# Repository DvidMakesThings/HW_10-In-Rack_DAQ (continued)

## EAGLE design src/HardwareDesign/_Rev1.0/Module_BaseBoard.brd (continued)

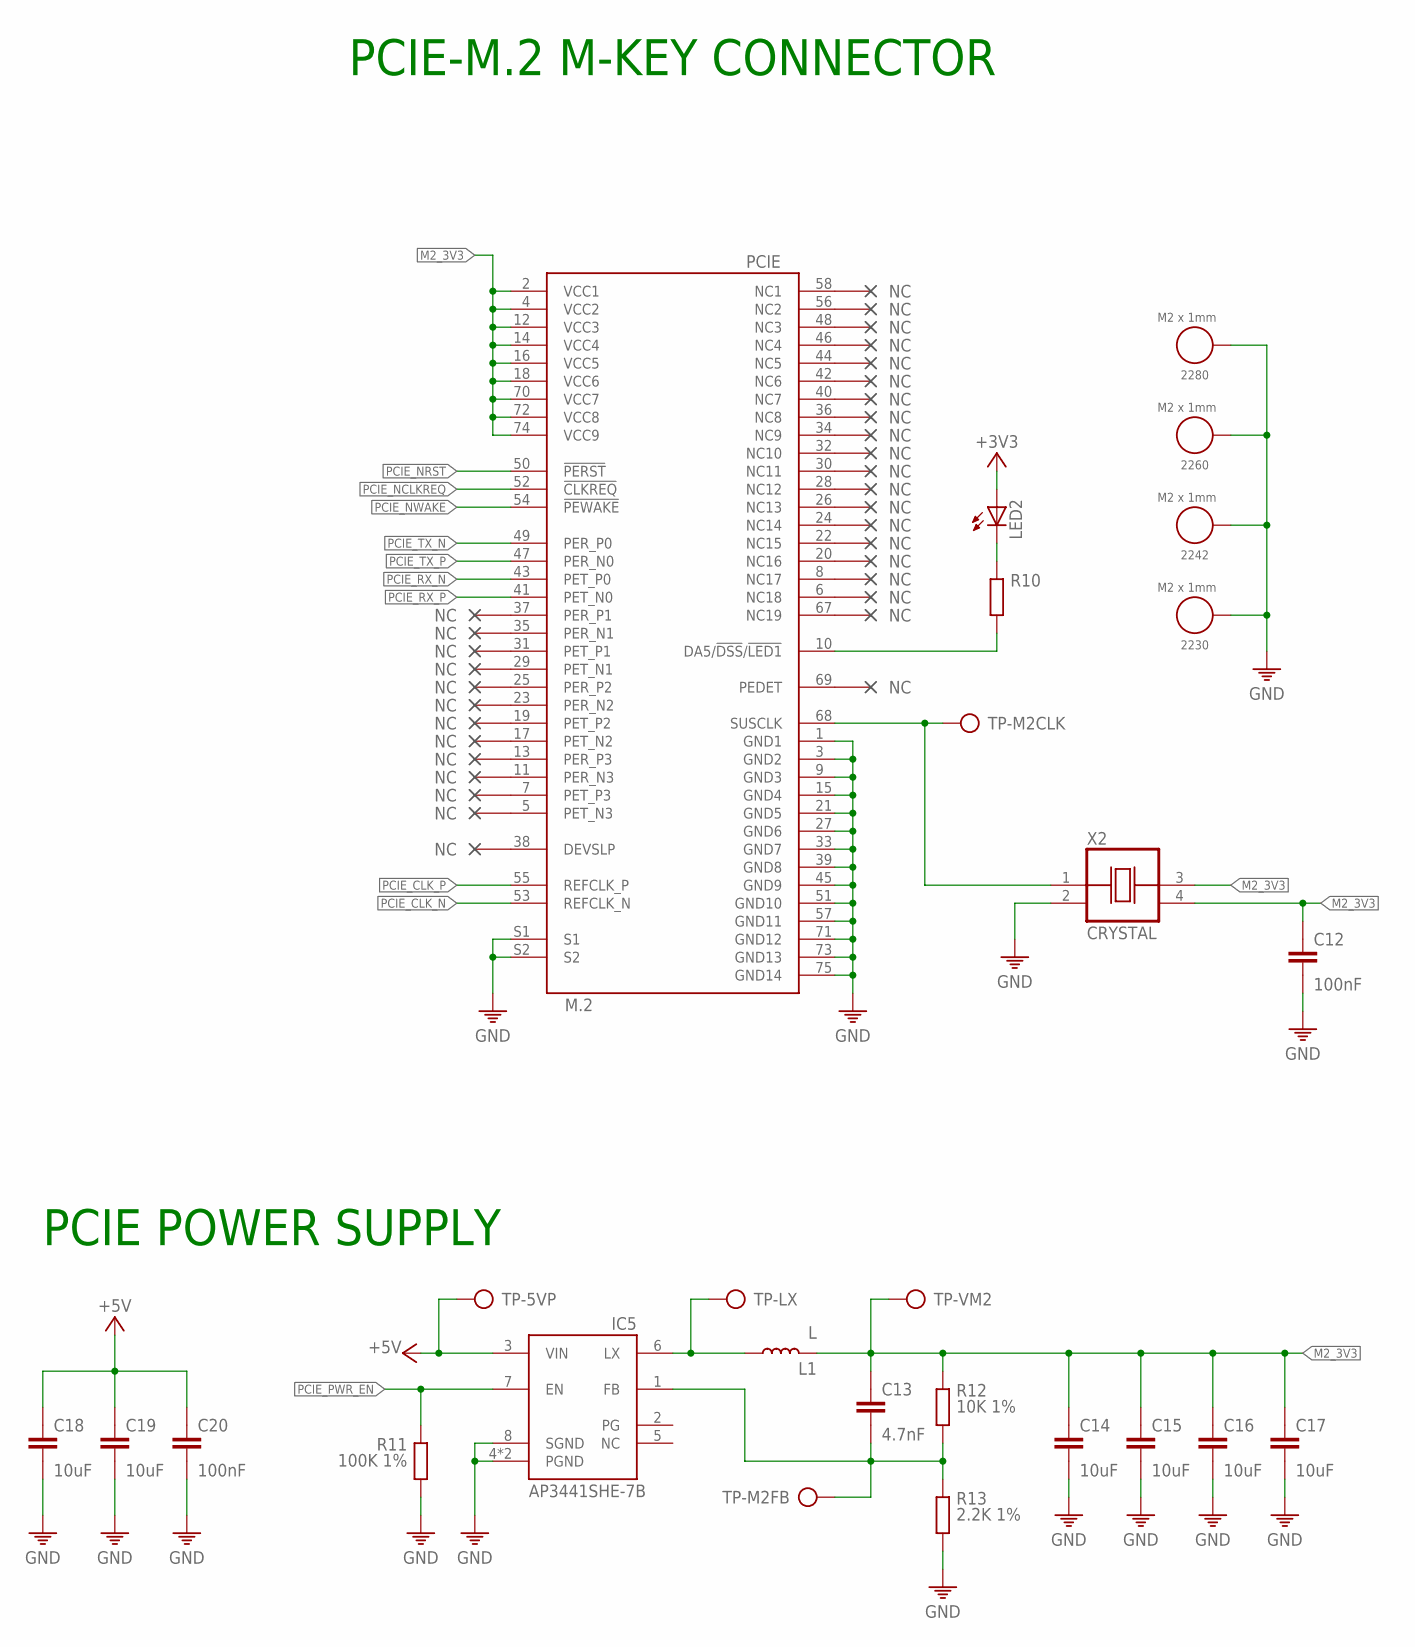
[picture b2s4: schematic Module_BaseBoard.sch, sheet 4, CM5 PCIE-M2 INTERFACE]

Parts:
2230, 2242, 2260, 2280: M2 x 1mm; WA-SMSI_9774010243
C12, C20: 100nF; C0402
C13: 4.7nF; C0402
C14, C15, C16, C17, C18, C19: 10uF; C0805
IC5: AP3441SHE-7B; SON50P201X201X56-9T90X170N
L1: L; SRR5228A
LED2: LEDCHIPLED_0805; CHIPLED_0805
PCIE: M.2
R10: R0402; 0402
R11: 100K 1%; 0402
R12: 10K 1%; 0402
R13: 2.2K 1%; 0402
TP-5VP: TP
TP-LX: TP
TP-M2CLK, TP-M2FB: TP
TP-VM2: TP
X2: CRYSTAL; OSCCC500X320X130

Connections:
+3V3: LED2.A; also elsewhere on the board
+5V: C18.1, C19.1, C20.1, IC5.3 (VIN), TP-5VP.TP; also elsewhere on the board
GND: 2230.1, 2242.1, 2260.1, 2280.1, C12.2, C14.2, C15.2, C16.2, C17.2, C18.2, C19.2, C20.2, IC5.4 (PGND), IC5.8 (SGND), IC5.9 (PGND), PCIE.1 (GND1), PCIE.3 (GND2), PCIE.9 (GND3), PCIE.15 (GND4), PCIE.21 (GND5), PCIE.27 (GND6), PCIE.33 (GND7), PCIE.39 (GND8), PCIE.45 (GND9), PCIE.51 (GND10), PCIE.57 (GND11), PCIE.71 (GND12), PCIE.73 (GND13), PCIE.75 (GND14), PCIE.S1, PCIE.S2, R11.2, R13.2, X2.2 (VSS); also elsewhere on the board
M2_3V3: C12.1, C13.1, C14.1, C15.1, C16.1, C17.1, L1.2, PCIE.2 (VCC1), PCIE.4 (VCC2), PCIE.12 (VCC3), PCIE.14 (VCC4), PCIE.16 (VCC5), PCIE.18 (VCC6), PCIE.70 (VCC7), PCIE.72 (VCC8), PCIE.74 (VCC9), R12.1, TP-VM2.TP, X2.3 (OUT), X2.4 (VDD)
unnamed: PCIE.10 (DA5/!DSS!/!LED1), R10.2
unnamed: LED2.C, R10.1
unnamed: IC5.6 (LX), L1.1, TP-LX.TP
unnamed: C13.2, IC5.1 (FB), R12.2, R13.1, TP-M2FB.TP
unnamed: PCIE.68 (SUSCLK), TP-M2CLK.TP, X2.1 (CON)
PCIE_CLK_N: PCIE.53 (REFCLK_N); also elsewhere on the board
PCIE_CLK_P: PCIE.55 (REFCLK_P); also elsewhere on the board
PCIE_NCLKREQ: PCIE.52 (!CLKREQ); also elsewhere on the board
PCIE_NRST: PCIE.50 (!PERST); also elsewhere on the board
PCIE_NWAKE: PCIE.54 (!PEWAKE); also elsewhere on the board
PCIE_PWR_EN: IC5.7 (EN), R11.1; also elsewhere on the board
PCIE_RX_N: PCIE.43 (PET_P0); also elsewhere on the board
PCIE_RX_P: PCIE.41 (PET_N0); also elsewhere on the board
PCIE_TX_N: PCIE.49 (PER_P0); also elsewhere on the board
PCIE_TX_P: PCIE.47 (PER_N0); also elsewhere on the board

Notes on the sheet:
PCIE-M.2 M-KEY CONNECTOR
PCIE POWER SUPPLY

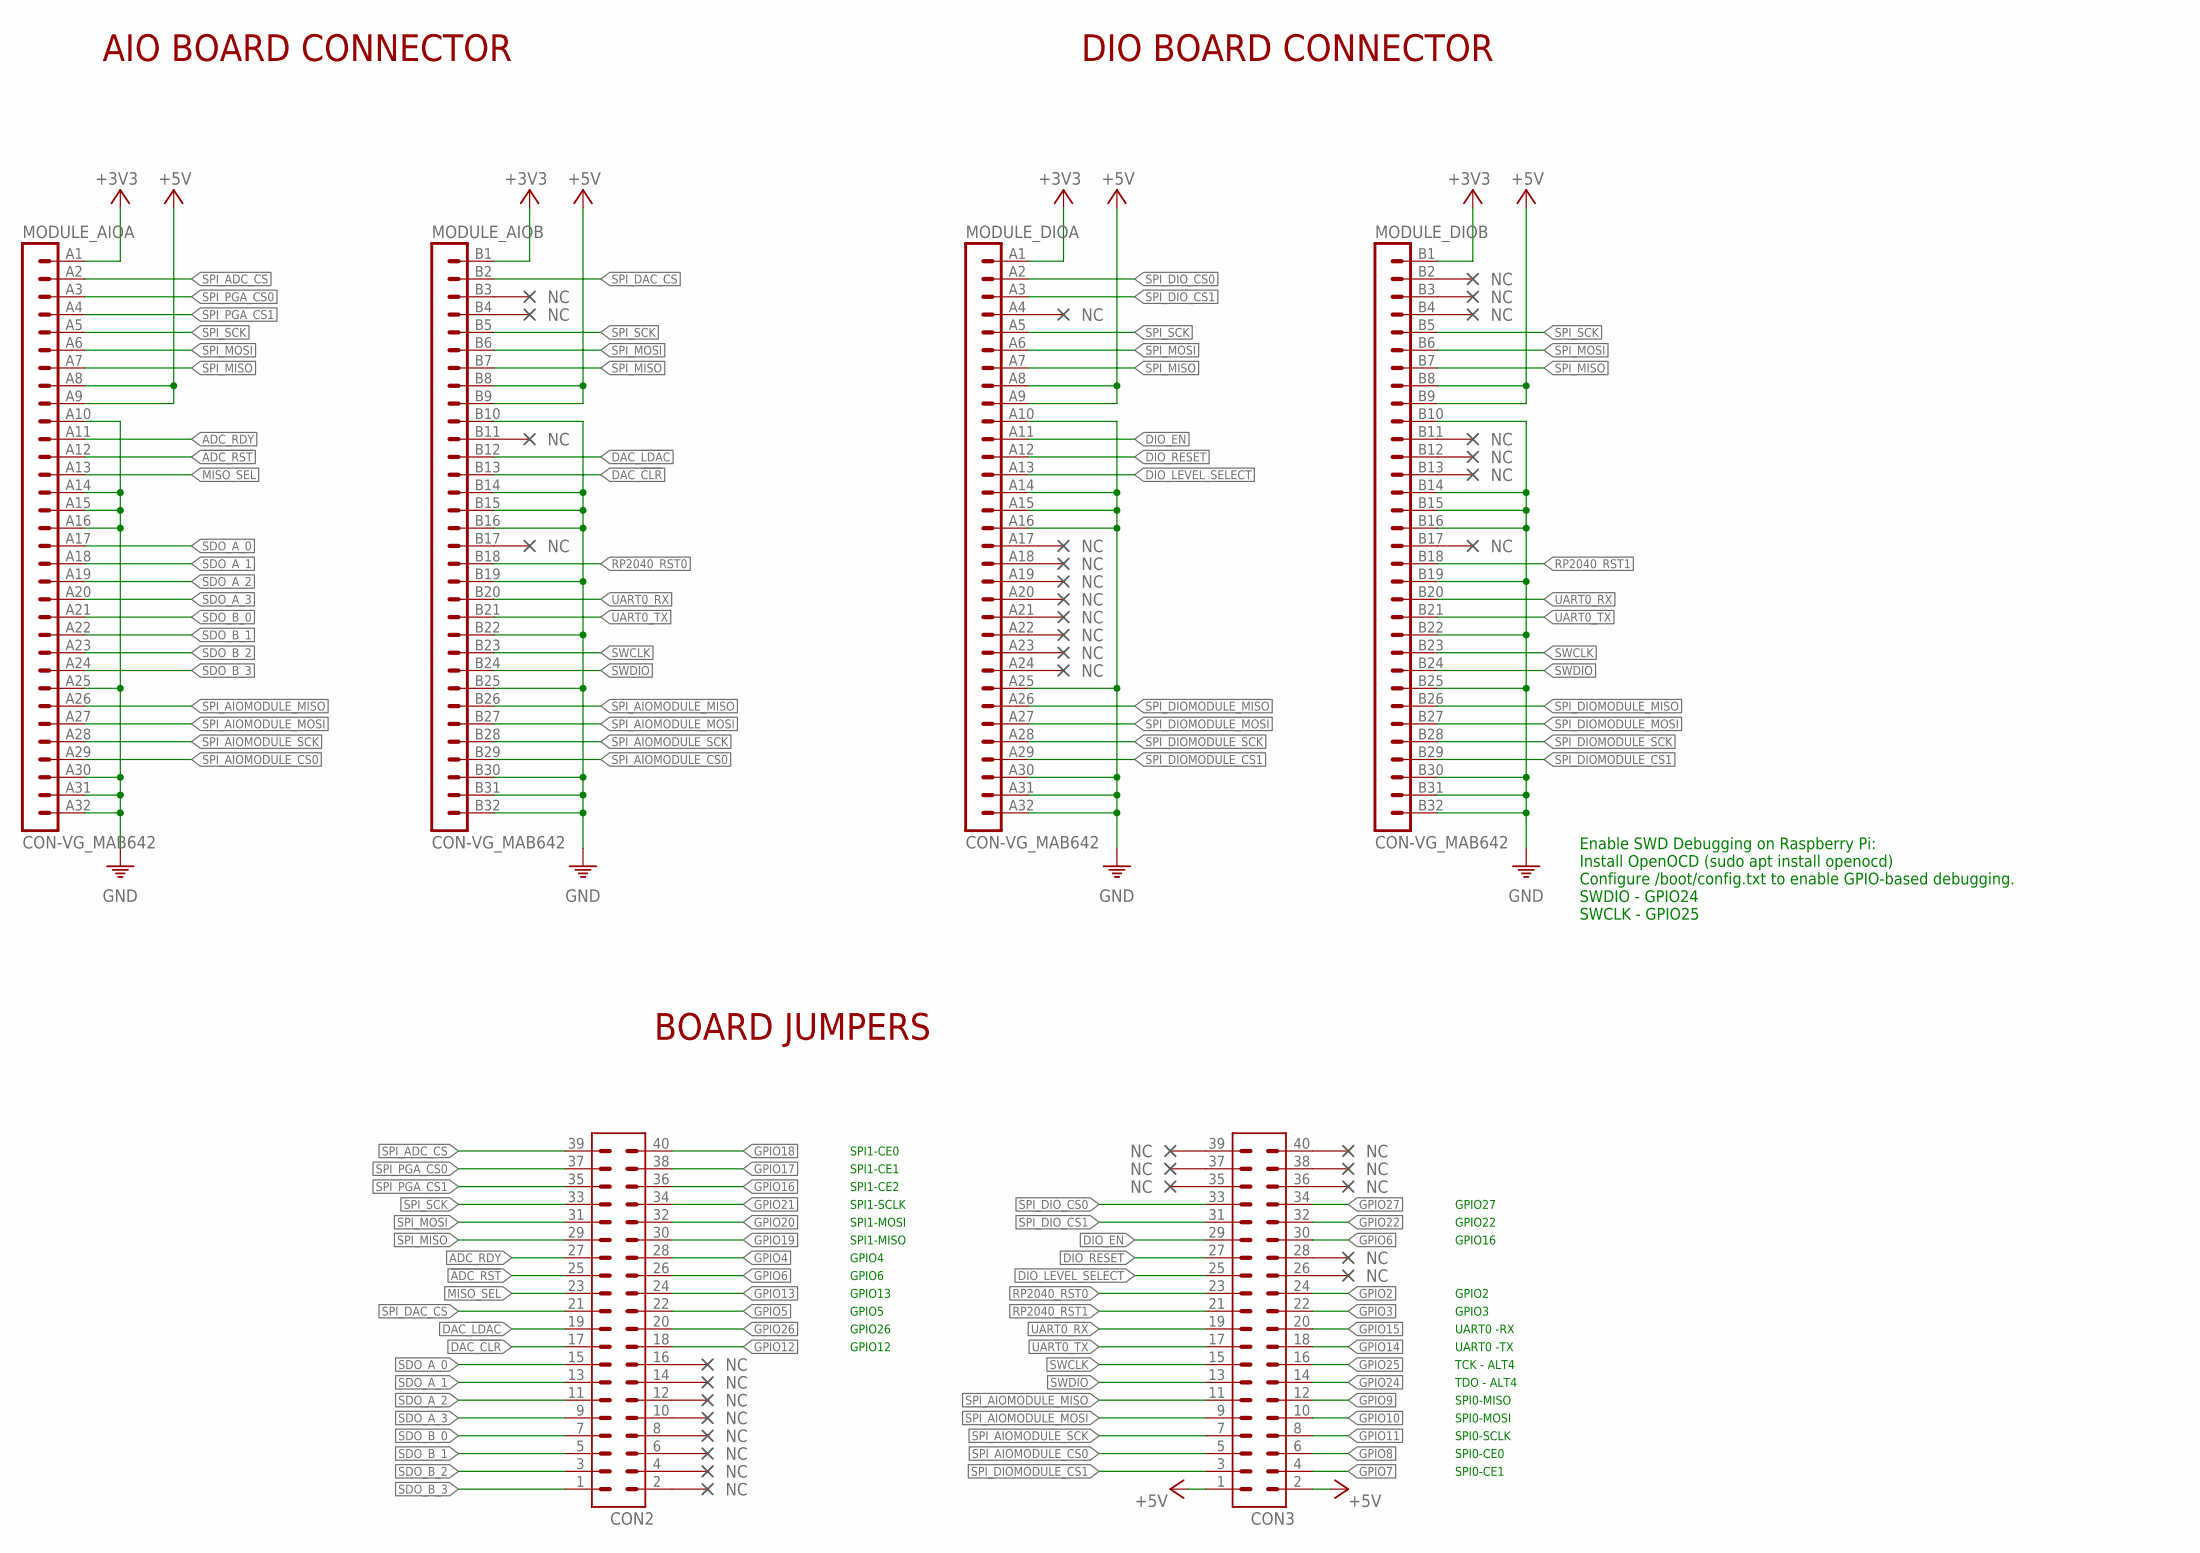
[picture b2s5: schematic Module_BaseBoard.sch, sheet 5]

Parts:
CON2, CON3: CON-2X20; 2X20
MODULE_AIO: CON-VG_MAB642; CON-VG-MAB64-RECEPTACLE
MODULE_DIO: CON-VG_MAB642; CON-VG-MAB64-RECEPTACLE

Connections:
!ADC_RST: CON2.25, MODULE_AIO.A12 (12)
+3V3: MODULE_AIO.A1 (1), MODULE_AIO.B1 (1), MODULE_DIO.A1 (1), MODULE_DIO.B1 (1); also elsewhere on the board
+5V: CON3.1, CON3.2, MODULE_AIO.A8 (8), MODULE_AIO.A9 (9), MODULE_AIO.B8 (8), MODULE_AIO.B9 (9), MODULE_DIO.A8 (8), MODULE_DIO.A9 (9), MODULE_DIO.B8 (8), MODULE_DIO.B9 (9); also elsewhere on the board
ADC_RDY: CON2.27, MODULE_AIO.A11 (11)
DAC_!CLR: CON2.17, MODULE_AIO.B13 (13)
DAC_!LDAC: CON2.19, MODULE_AIO.B12 (12)
DIO_EN: CON3.29, MODULE_DIO.A11 (11)
DIO_LEVEL_SELECT: CON3.25, MODULE_DIO.A13 (13)
DIO_RESET: CON3.27, MODULE_DIO.A12 (12)
GND: MODULE_AIO.A10 (10), MODULE_AIO.A14 (14), MODULE_AIO.A15 (15), MODULE_AIO.A16 (16), MODULE_AIO.A25 (25), MODULE_AIO.A30 (30), MODULE_AIO.A31 (31), MODULE_AIO.A32 (32), MODULE_AIO.B10 (10), MODULE_AIO.B14 (14), MODULE_AIO.B15 (15), MODULE_AIO.B16 (16), MODULE_AIO.B19 (19), MODULE_AIO.B22 (22), MODULE_AIO.B25 (25), MODULE_AIO.B30 (30), MODULE_AIO.B31 (31), MODULE_AIO.B32 (32), MODULE_DIO.A10 (10), MODULE_DIO.A14 (14), MODULE_DIO.A15 (15), MODULE_DIO.A16 (16), MODULE_DIO.A25 (25), MODULE_DIO.A30 (30), MODULE_DIO.A31 (31), MODULE_DIO.A32 (32), MODULE_DIO.B10 (10), MODULE_DIO.B14 (14), MODULE_DIO.B15 (15), MODULE_DIO.B16 (16), MODULE_DIO.B19 (19), MODULE_DIO.B22 (22), MODULE_DIO.B25 (25), MODULE_DIO.B30 (30), MODULE_DIO.B31 (31), MODULE_DIO.B32 (32); also elsewhere on the board
GPIO2: CON3.24; also elsewhere on the board
GPIO3: CON3.22; also elsewhere on the board
GPIO4: CON2.28; also elsewhere on the board
GPIO5: CON2.22; also elsewhere on the board
GPIO6: CON2.26, CON3.30; also elsewhere on the board
GPIO7: CON3.4; also elsewhere on the board
GPIO8: CON3.6; also elsewhere on the board
GPIO9: CON3.12; also elsewhere on the board
GPIO10: CON3.10; also elsewhere on the board
GPIO11: CON3.8; also elsewhere on the board
GPIO12: CON2.18; also elsewhere on the board
GPIO13: CON2.24; also elsewhere on the board
GPIO14: CON3.18; also elsewhere on the board
GPIO15: CON3.20; also elsewhere on the board
GPIO16: CON2.36; also elsewhere on the board
GPIO17: CON2.38; also elsewhere on the board
GPIO18: CON2.40; also elsewhere on the board
GPIO19: CON2.30; also elsewhere on the board
GPIO20: CON2.32; also elsewhere on the board
GPIO21: CON2.34; also elsewhere on the board
GPIO22: CON3.32; also elsewhere on the board
GPIO24: CON3.14; also elsewhere on the board
GPIO25: CON3.16; also elsewhere on the board
GPIO26: CON2.20; also elsewhere on the board
GPIO27: CON3.34; also elsewhere on the board
MISO_SEL: CON2.23, MODULE_AIO.A13 (13)
RP2040_RST0: CON3.23, MODULE_AIO.B18 (18)
RP2040_RST1: CON3.21, MODULE_DIO.B18 (18)
SDO_A_0: CON2.15, MODULE_AIO.A17 (17)
SDO_A_1: CON2.13, MODULE_AIO.A18 (18)
SDO_A_2: CON2.11, MODULE_AIO.A19 (19)
SDO_A_3: CON2.9, MODULE_AIO.A20 (20)
SDO_B_0: CON2.7, MODULE_AIO.A21 (21)
SDO_B_1: CON2.5, MODULE_AIO.A22 (22)
SDO_B_2: CON2.3, MODULE_AIO.A23 (23)
SDO_B_3: CON2.1, MODULE_AIO.A24 (24)
SPI_ADC_CS: CON2.39, MODULE_AIO.A2 (2)
SPI_AIOMODULE_CS0: CON3.5, MODULE_AIO.A29 (29), MODULE_AIO.B29 (29)
SPI_AIOMODULE_MISO: CON3.11, MODULE_AIO.A26 (26), MODULE_AIO.B26 (26)
SPI_AIOMODULE_MOSI: CON3.9, MODULE_AIO.A27 (27), MODULE_AIO.B27 (27)
SPI_AIOMODULE_SCK: CON3.7, MODULE_AIO.A28 (28), MODULE_AIO.B28 (28)
SPI_DAC_CS: CON2.21, MODULE_AIO.B2 (2)
SPI_DIOMODULE_CS1: CON3.3, MODULE_DIO.A29 (29), MODULE_DIO.B29 (29)
SPI_DIOMODULE_MISO: MODULE_DIO.A26 (26), MODULE_DIO.B26 (26)
SPI_DIOMODULE_MOSI: MODULE_DIO.A27 (27), MODULE_DIO.B27 (27)
SPI_DIOMODULE_SCK: MODULE_DIO.A28 (28), MODULE_DIO.B28 (28)
SPI_DIO_CS0: CON3.33, MODULE_DIO.A2 (2)
SPI_DIO_CS1: CON3.31, MODULE_DIO.A3 (3)
SPI_MISO: CON2.29, MODULE_AIO.A7 (7), MODULE_AIO.B7 (7), MODULE_DIO.A7 (7), MODULE_DIO.B7 (7)
SPI_MOSI: CON2.31, MODULE_AIO.A6 (6), MODULE_AIO.B6 (6), MODULE_DIO.A6 (6), MODULE_DIO.B6 (6)
SPI_PGA_CS0: CON2.37, MODULE_AIO.A3 (3)
SPI_PGA_CS1: CON2.35, MODULE_AIO.A4 (4)
SPI_SCK: CON2.33, MODULE_AIO.A5 (5), MODULE_AIO.B5 (5), MODULE_DIO.A5 (5), MODULE_DIO.B5 (5)
SWCLK: CON3.15, MODULE_AIO.B23 (23), MODULE_DIO.B23 (23)
SWDIO: CON3.13, MODULE_AIO.B24 (24), MODULE_DIO.B24 (24)
UART0_RX: CON3.19, MODULE_AIO.B20 (20), MODULE_DIO.B20 (20)
UART0_TX: CON3.17, MODULE_AIO.B21 (21), MODULE_DIO.B21 (21)

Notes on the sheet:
AIO BOARD CONNECTOR
Enable SWD Debugging on Raspberry Pi: Install OpenOCD (sudo apt install openocd) Configure /boot/config.txt to enable GPIO-based debugging. SWDIO - GPIO24 SWCLK - GPIO25
DIO BOARD CONNECTOR
BOARD JUMPERS
SPI1-CE0
SPI1-CE1
SPI1-CE2
SPI1-SCLK
SPI1-MOSI
SPI1-MISO
GPIO5
GPIO27
GPIO22
TDO - ALT4
TCK - ALT4
UART0 -RX
UART0 -TX
SPI0-MISO
SPI0-MOSI
SPI0-SCLK
SPI0-CE0
SPI0-CE1
GPIO4
GPIO6
GPIO13
GPIO26
GPIO12
GPIO16
GPIO2
GPIO3

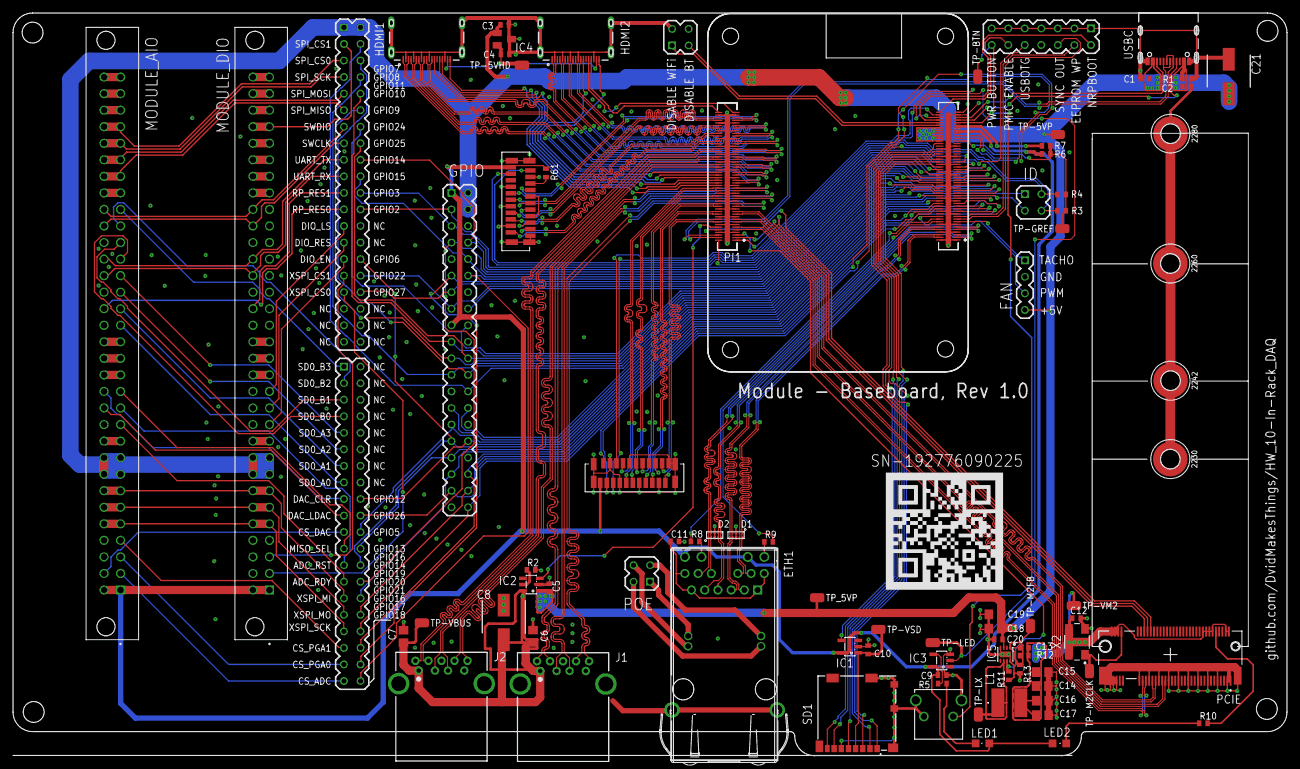
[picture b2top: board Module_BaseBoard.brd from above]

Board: 4 copper layers, 195.6 x 114.0 mm, 84 parts (0 on the bottom side), 197 nets.

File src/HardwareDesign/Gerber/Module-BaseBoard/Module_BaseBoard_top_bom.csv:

Comment,Designator,Footprint,LCSC Part #
,C1 C2,C0402,
,LED2,CHIPLED_0805,
,PI1,CM5,
,R10,0402,
,SD1,MICROSD,
0R,R6,0402,
1K,R5,0402,
2.2K 1%,R1 R3 R4 R13 R61,0402,
4.7nF,C13,C0402,
10K 1%,R12,0402,
10uF,C6 C7 C14 C15 C16 C17 C18 C19,C0805,
15K 1%,R2,0402,
74LVC1G07,IC3,SOT23-5,
100K 1%,R11,0402,
100nF,C3 C4 C5 C9 C10 C11 C12 C20,C0402,
100uF 16V,C8 C21,100UF-16V,
470R,R8 R9,0402,
629722000214,USBC,629722000214,
685119136923,HDMI1 HDMI2,685119136923,
AP3441SHE-7B,IC5,SON50P201X201X56-9T90X170N,
AP22653W6,IC2,SOT23-6,
CRYSTAL,X2,OSCCC500X320X130,
DNI,R7,0402,
FH12-22S-0.5SVA,J3 J4,FH12-22S-0.5SH,
Green,LED1,CHIPLED_0805,
L,L1,SRR5228A,
M.2,PCIE,M.2,
M2 x 1mm,2230 2242 2260 2280,WA-SMSI_9774010243,
RT9742GGJ,IC1,SOT23-5,
RT9742NGV,IC4,SOT23,
TP,TP-5VHD TP-5VP TP-BTN TP-GREF TP-LED TP-LX TP-M2CLK TP-M2FB TP-VBUS TP-VM2 TP-VSD TP_5VP,TP,
TPD4EUSB30,D1 D2,USON,

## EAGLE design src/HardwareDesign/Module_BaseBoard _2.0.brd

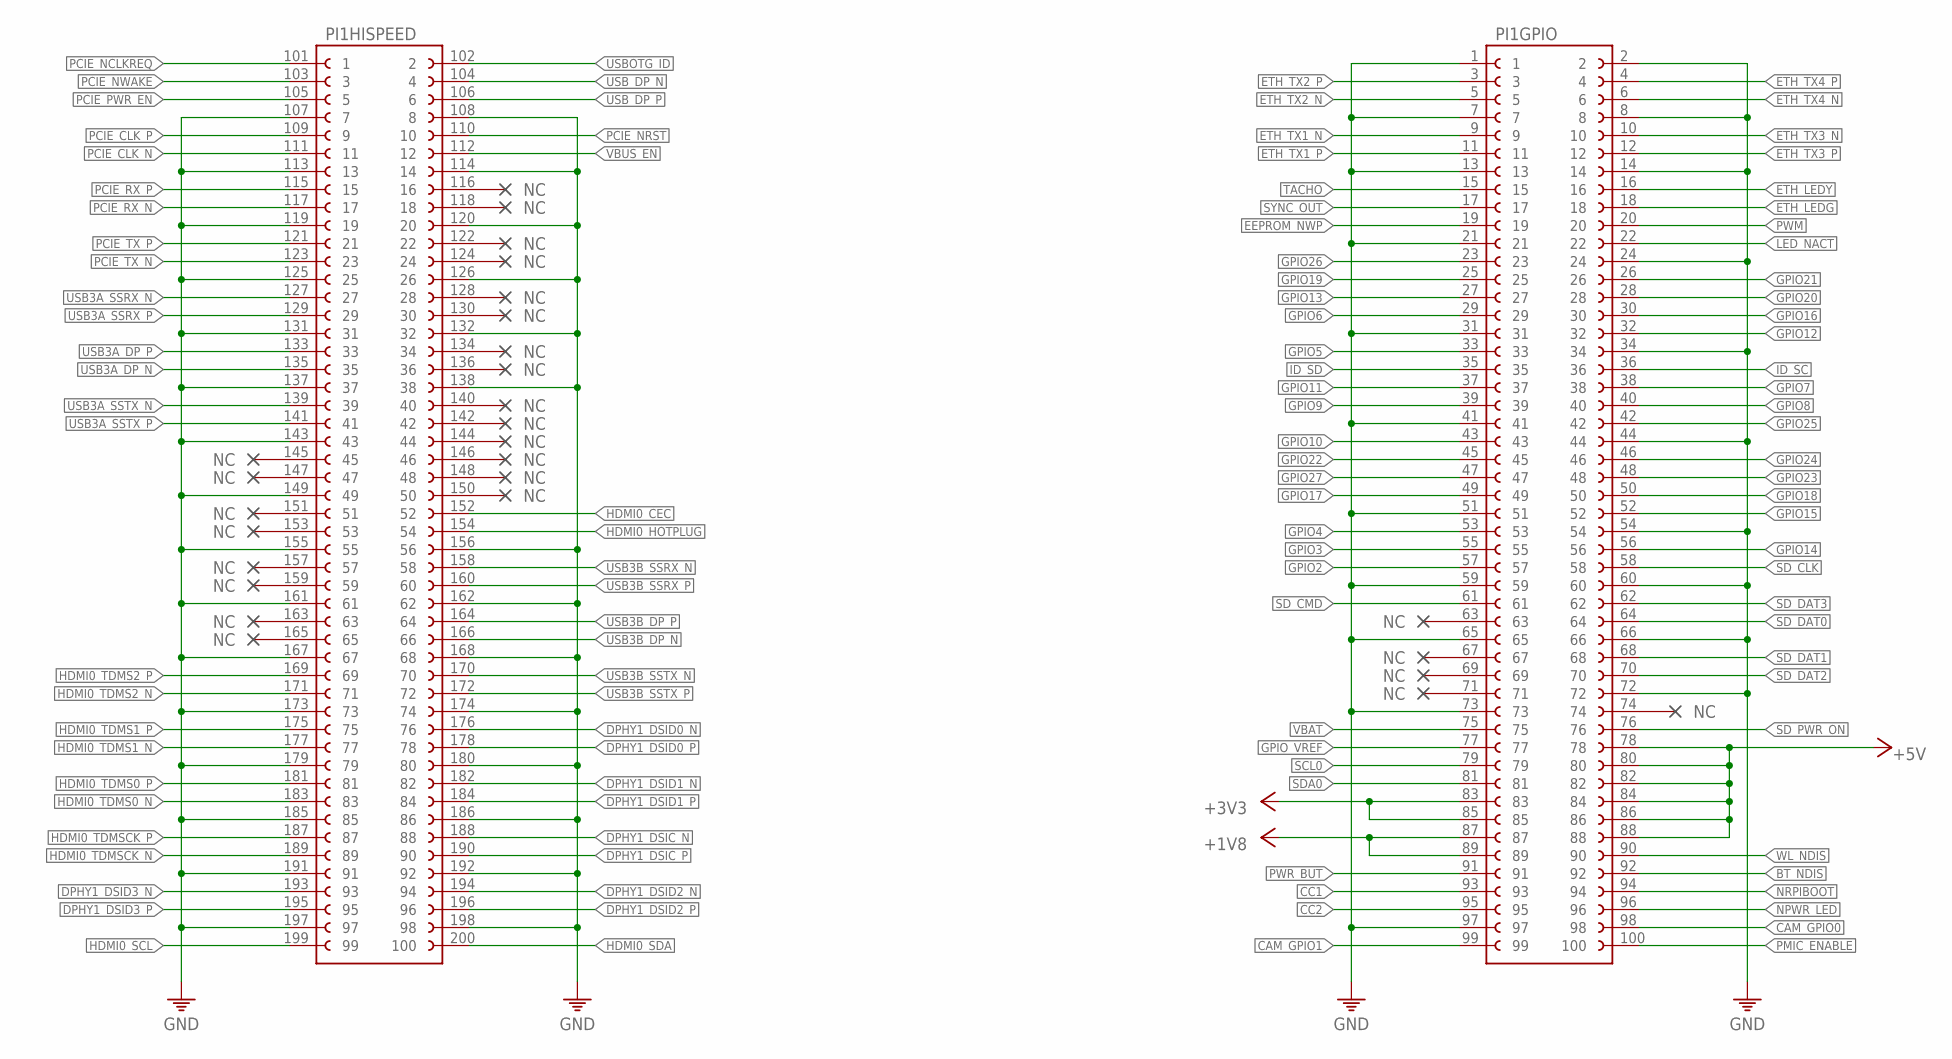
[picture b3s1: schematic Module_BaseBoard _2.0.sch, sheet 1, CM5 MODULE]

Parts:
PI1: RASPBERRY_CM5; CM5

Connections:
+1V8: PI1.87, PI1.89; also elsewhere on the board
+3V3: PI1.83, PI1.85; also elsewhere on the board
+5V: PI1.78, PI1.80, PI1.82, PI1.84, PI1.86, PI1.88; also elsewhere on the board
BT_NDIS: PI1.92
CAM_GPIO0: PI1.98; also elsewhere on the board
CAM_GPIO1: PI1.99; also elsewhere on the board
CC1: PI1.93; also elsewhere on the board
CC2: PI1.95; also elsewhere on the board
DPHY1_DSIC_N: PI1.188 (88); also elsewhere on the board
DPHY1_DSIC_P: PI1.190 (90); also elsewhere on the board
DPHY1_DSID0_N: PI1.176 (76); also elsewhere on the board
DPHY1_DSID0_P: PI1.178 (78); also elsewhere on the board
DPHY1_DSID1_N: PI1.182 (82); also elsewhere on the board
DPHY1_DSID1_P: PI1.184 (84); also elsewhere on the board
DPHY1_DSID2_N: PI1.194 (94); also elsewhere on the board
DPHY1_DSID2_P: PI1.196 (96); also elsewhere on the board
DPHY1_DSID3_N: PI1.193 (93); also elsewhere on the board
DPHY1_DSID3_P: PI1.195 (95); also elsewhere on the board
EEPROM_NWP: PI1.19; also elsewhere on the board
ETH_LEDG: PI1.18; also elsewhere on the board
ETH_LEDY: PI1.16; also elsewhere on the board
ETH_TX1_N: PI1.9; also elsewhere on the board
ETH_TX1_P: PI1.11; also elsewhere on the board
ETH_TX2_N: PI1.5; also elsewhere on the board
ETH_TX2_P: PI1.3; also elsewhere on the board
ETH_TX3_N: PI1.10; also elsewhere on the board
ETH_TX3_P: PI1.12; also elsewhere on the board
ETH_TX4_N: PI1.6; also elsewhere on the board
ETH_TX4_P: PI1.4; also elsewhere on the board
GND: PI1.1, PI1.2, PI1.7, PI1.8, PI1.13, PI1.14, PI1.21, PI1.24, PI1.31, PI1.34, PI1.41, PI1.44, PI1.51, PI1.54, PI1.59, PI1.60, PI1.65, PI1.66, PI1.72, PI1.73, PI1.97, PI1.107 (7), PI1.108 (8), PI1.113 (13), PI1.114 (14), PI1.119 (19), PI1.120 (20), PI1.125 (25), PI1.126 (26), PI1.131 (31), PI1.132 (32), PI1.137 (37), PI1.138 (38), PI1.143 (43), PI1.149 (49), PI1.155 (55), PI1.156 (56), PI1.161 (61), PI1.162 (62), PI1.167 (67), PI1.168 (68), PI1.173 (73), PI1.174 (74), PI1.179 (79), PI1.180 (80), PI1.185 (85), PI1.186 (86), PI1.191 (91), PI1.192 (92), PI1.197 (97), PI1.198 (98); also elsewhere on the board
GPIO2: PI1.57; also elsewhere on the board
GPIO3: PI1.55; also elsewhere on the board
GPIO4: PI1.53; also elsewhere on the board
GPIO5: PI1.33; also elsewhere on the board
GPIO6: PI1.29; also elsewhere on the board
GPIO7: PI1.38; also elsewhere on the board
GPIO8: PI1.40; also elsewhere on the board
GPIO9: PI1.39; also elsewhere on the board
GPIO10: PI1.43; also elsewhere on the board
GPIO11: PI1.37; also elsewhere on the board
GPIO12: PI1.32; also elsewhere on the board
GPIO13: PI1.27; also elsewhere on the board
GPIO14: PI1.56; also elsewhere on the board
GPIO15: PI1.52; also elsewhere on the board
GPIO16: PI1.30; also elsewhere on the board
GPIO17: PI1.49; also elsewhere on the board
GPIO18: PI1.50; also elsewhere on the board
GPIO19: PI1.25; also elsewhere on the board
GPIO20: PI1.28; also elsewhere on the board
GPIO21: PI1.26; also elsewhere on the board
GPIO22: PI1.45; also elsewhere on the board
GPIO23: PI1.48; also elsewhere on the board
GPIO24: PI1.46; also elsewhere on the board
GPIO25: PI1.42; also elsewhere on the board
GPIO26: PI1.23; also elsewhere on the board
GPIO27: PI1.47; also elsewhere on the board
GPIO_VREF: PI1.77; also elsewhere on the board
HDMI0_CEC: PI1.152 (52); also elsewhere on the board
HDMI0_HOTPLUG: PI1.154 (54); also elsewhere on the board
HDMI0_SCL: PI1.199 (99); also elsewhere on the board
HDMI0_SDA: PI1.200 (100); also elsewhere on the board
HDMI0_TDMS0_N: PI1.183 (83); also elsewhere on the board
HDMI0_TDMS0_P: PI1.181 (81); also elsewhere on the board
HDMI0_TDMS1_N: PI1.177 (77); also elsewhere on the board
HDMI0_TDMS1_P: PI1.175 (75); also elsewhere on the board
HDMI0_TDMS2_N: PI1.171 (71); also elsewhere on the board
HDMI0_TDMS2_P: PI1.169 (69); also elsewhere on the board
HDMI0_TDMSCK_N: PI1.189 (89); also elsewhere on the board
HDMI0_TDMSCK_P: PI1.187 (87); also elsewhere on the board
ID_SC: PI1.36; also elsewhere on the board
ID_SD: PI1.35; also elsewhere on the board
LED_NACT: PI1.22; also elsewhere on the board
NPWR_LED: PI1.96; also elsewhere on the board
NRPIBOOT: PI1.94; also elsewhere on the board
PCIE_CLK_N: PI1.111 (11); also elsewhere on the board
PCIE_CLK_P: PI1.109 (9); also elsewhere on the board
PCIE_NCLKREQ: PI1.101 (1); also elsewhere on the board
PCIE_NRST: PI1.110 (10); also elsewhere on the board
PCIE_NWAKE: PI1.103 (3); also elsewhere on the board
PCIE_PWR_EN: PI1.105 (5); also elsewhere on the board
PCIE_RX_N: PI1.117 (17); also elsewhere on the board
PCIE_RX_P: PI1.115 (15); also elsewhere on the board
PCIE_TX_N: PI1.123 (23); also elsewhere on the board
PCIE_TX_P: PI1.121 (21); also elsewhere on the board
PMIC_ENABLE: PI1.100; also elsewhere on the board
PWM: PI1.20
PWR_BUT: PI1.91; also elsewhere on the board
SCL0: PI1.79
SDA0: PI1.81
SD_CLK: PI1.58; also elsewhere on the board
SD_CMD: PI1.61; also elsewhere on the board
SD_DAT0: PI1.64; also elsewhere on the board
SD_DAT1: PI1.68; also elsewhere on the board
SD_DAT2: PI1.70; also elsewhere on the board
SD_DAT3: PI1.62; also elsewhere on the board
SD_PWR_ON: PI1.76; also elsewhere on the board
SYNC_OUT: PI1.17; also elsewhere on the board
TACHO: PI1.15
USB3A_DP_N: PI1.135 (35); also elsewhere on the board
USB3A_DP_P: PI1.133 (33); also elsewhere on the board
USB3A_SSRX_N: PI1.127 (27); also elsewhere on the board
USB3A_SSRX_P: PI1.129 (29); also elsewhere on the board
USB3A_SSTX_N: PI1.139 (39); also elsewhere on the board
USB3A_SSTX_P: PI1.141 (41); also elsewhere on the board
USB3B_DP_N: PI1.166 (66); also elsewhere on the board
USB3B_DP_P: PI1.164 (64); also elsewhere on the board
USB3B_SSRX_N: PI1.158 (58); also elsewhere on the board
USB3B_SSRX_P: PI1.160 (60); also elsewhere on the board
USB3B_SSTX_N: PI1.170 (70); also elsewhere on the board
USB3B_SSTX_P: PI1.172 (72); also elsewhere on the board
USBOTG_ID: PI1.102 (2); also elsewhere on the board
USB_DP_N: PI1.104 (4); also elsewhere on the board
USB_DP_P: PI1.106 (6); also elsewhere on the board
VBAT: PI1.75
VBUS_EN: PI1.112 (12); also elsewhere on the board
WL_NDIS: PI1.90

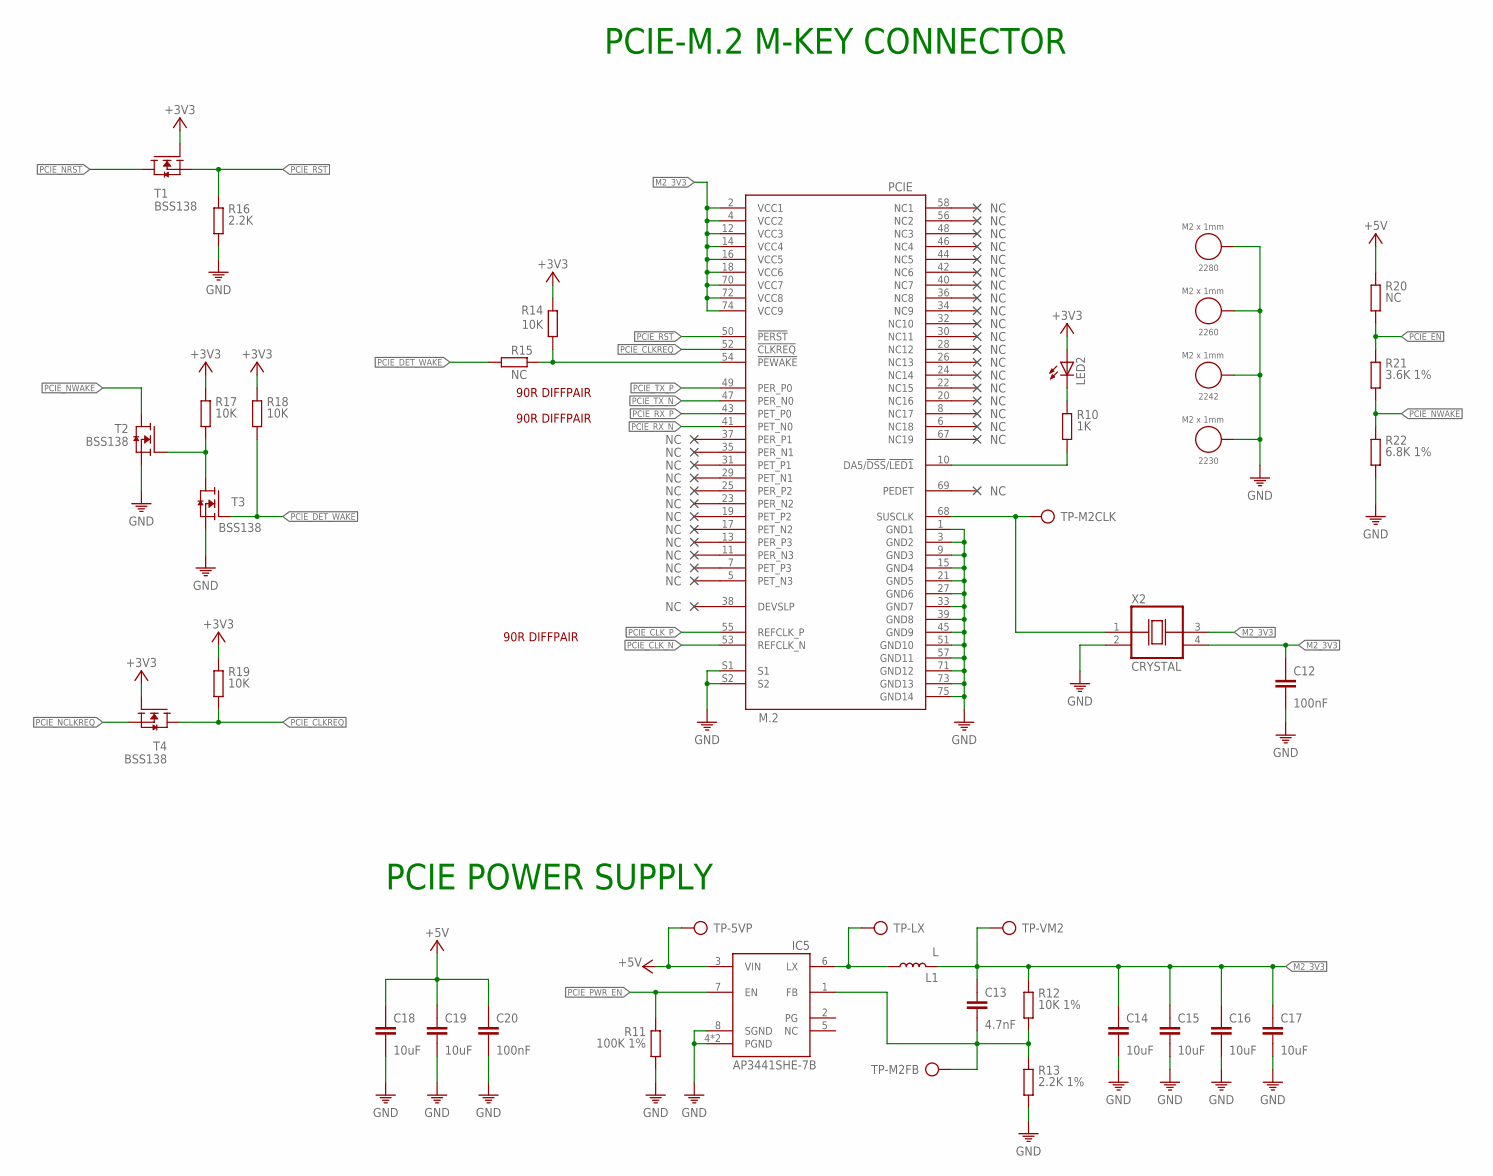
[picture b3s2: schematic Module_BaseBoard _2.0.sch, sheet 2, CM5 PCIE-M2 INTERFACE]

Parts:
2230, 2242, 2260, 2280: M2 x 1mm; WA-SMSI_9774010243
C12, C20: 100nF; C0402
C13: 4.7nF; C0402
C14, C15, C16, C17, C18, C19: 10uF; C0805
IC5: AP3441SHE-7B; SON50P201X201X56-9T90X170N
L1: L; SRR5228A
LED2: LEDCHIPLED_0805; CHIPLED_0805
PCIE: M.2; PCIE_M.2
R10: 1K; 0402
R11: 100K 1%; 0402
R12: 10K 1%; 0402
R13: 2.2K 1%; 0402
R14, R17, R18, R19: 10K; 0402
R15, R20: NC; 0402
R16: 2.2K; 0402
R21: 3.6K 1%; 0402
R22: 6.8K 1%; 0402
T1, T2, T3, T4: BSS138; SOT23
TP-5VP: TP
TP-LX: TP
TP-M2CLK, TP-M2FB: TP
TP-VM2: TP
X2: CRYSTAL; OSCCC500X320X130

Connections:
+3V3: LED2.A, R14.1, R17.1, R18.1, R19.1, T1.1 (G), T4.1 (G); also elsewhere on the board
+5V: C18.1, C19.1, C20.1, IC5.3 (VIN), R20.1, TP-5VP.TP; also elsewhere on the board
GND: 2230.1, 2242.1, 2260.1, 2280.1, C12.2, C14.2, C15.2, C16.2, C17.2, C18.2, C19.2, C20.2, IC5.4 (PGND), IC5.8 (SGND), IC5.9 (PGND), PCIE.1 (GND1), PCIE.3 (GND2), PCIE.9 (GND3), PCIE.15 (GND4), PCIE.21 (GND5), PCIE.27 (GND6), PCIE.33 (GND7), PCIE.39 (GND8), PCIE.45 (GND9), PCIE.51 (GND10), PCIE.57 (GND11), PCIE.71 (GND12), PCIE.73 (GND13), PCIE.75 (GND14), PCIE.S1, PCIE.S2, R11.2, R13.2, R16.2, R22.2, T2.2 (S), T3.2 (S), X2.2 (VSS); also elsewhere on the board
M2_3V3: C12.1, C13.1, C14.1, C15.1, C16.1, C17.1, L1.2, PCIE.2 (VCC1), PCIE.4 (VCC2), PCIE.12 (VCC3), PCIE.14 (VCC4), PCIE.16 (VCC5), PCIE.18 (VCC6), PCIE.70 (VCC7), PCIE.72 (VCC8), PCIE.74 (VCC9), R12.1, TP-VM2.TP, X2.3 (OUT), X2.4 (VDD)
unnamed: PCIE.10 (DA5/!DSS!/!LED1), R10.2
unnamed: LED2.C, R10.1
unnamed: IC5.6 (LX), L1.1, TP-LX.TP
unnamed: C13.2, IC5.1 (FB), R12.2, R13.1, TP-M2FB.TP
unnamed: PCIE.68 (SUSCLK), TP-M2CLK.TP, X2.1 (CON)
unnamed: PCIE.54 (!PEWAKE), R14.2, R15.1
unnamed: R17.2, T2.1 (G), T3.3 (D)
PCIE_CLKREQ: PCIE.52 (!CLKREQ), R19.2, T4.3 (D)
PCIE_CLK_N: PCIE.53 (REFCLK_N); also elsewhere on the board
PCIE_CLK_P: PCIE.55 (REFCLK_P); also elsewhere on the board
PCIE_DET_WAKE: R15.2, R18.2, T3.1 (G)
PCIE_EN: R20.2, R21.1
PCIE_NCLKREQ: T4.2 (S); also elsewhere on the board
PCIE_NRST: T1.3 (D); also elsewhere on the board
PCIE_NWAKE: R21.2, R22.1, T2.3 (D); also elsewhere on the board
PCIE_PWR_EN: IC5.7 (EN), R11.1; also elsewhere on the board
PCIE_RST: PCIE.50 (!PERST), R16.1, T1.2 (S)
PCIE_RX_N: PCIE.41 (PET_N0); also elsewhere on the board
PCIE_RX_P: PCIE.43 (PET_P0); also elsewhere on the board
PCIE_TX_N: PCIE.47 (PER_N0); also elsewhere on the board
PCIE_TX_P: PCIE.49 (PER_P0); also elsewhere on the board

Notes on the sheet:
PCIE-M.2 M-KEY CONNECTOR
PCIE POWER SUPPLY
90R DIFFPAIR
